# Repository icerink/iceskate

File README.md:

# iceskate

A low cost FPGA development board for absolute newbies.

## Why?
Getting started with FPGA design is hard. Unnecessarily hard.

## How?
Everyone knows how to use a browser. Many people know (some) webdesign.

The [*icerink*](https://github.com/icerink) ecosystem tries to exploit this by building a complete browser centric FPGA workflow. Edit, synthesize and upload FPGA designs from within your browser.

Doing this lowers the boarding hurdle by not requiring the installation of toolchains. Just plug in the board and begin to play :).

## What?
Mainly a FPGA and a USB interface. Not much more. 

The main source of inspiration for this board was the [upduino](http://gnarlygrey.atspace.cc/development-platform.html) by Gnarly Grey. We tried to build a similarly minimal and cheap board. The main Hardware feature, our board employs additionally, is the Microcontroller that is capable of speaking a wide variety of USB-Protocols.

In the *icerink* ecosystem, this capability is used to access the FPGA board from within the browser. 

The iceskate board features:
* The [ICE40UP5K](http://datasheet.octopart.com/ICE40UP5K-SG48ITR50-Lattice-Semiconductor-datasheet-101745901.pdf) FPGA (with experimential support in project icestorm, an open source fpga toolchain)
* An [STM32F070F6P6](http://datasheet.octopart.com/STM32F070F6P6-STMicroelectronics-datasheet-36993117.pdf)
* A single user definable push button and
* A user definable LED

## How to get one?
Build one yourself!

The board is optimized for hand soldering and has a [BOM cost](https://octopart.com/bom-tool/w8mU938s) of ~10€ when you build 10. The PCB can be ordered online at most common PCB manufacturers. We Ordered our boards at jlcpcb. 
[Assembly instructiost can be found here.](https://icerink.github.io/iceskate/)

## Can I help?
Definitely.

If you want to contribute to the hardware design or help with any other thing, do not hesitate to use the issue tracker to get in touch :).

However, it would be nice if you talk to us, **before** you start writing code and invest your time ;).

To develop the board, clone this repository with 
`git clone --recursive https://github.com/icerink/iceskate`.
Then you can simply use Kicad to edit the scematics and PCB.

```diff
- Warning!
- This Project uses submodules! when you clone without --recursive Kicad wont find some libraries!
```

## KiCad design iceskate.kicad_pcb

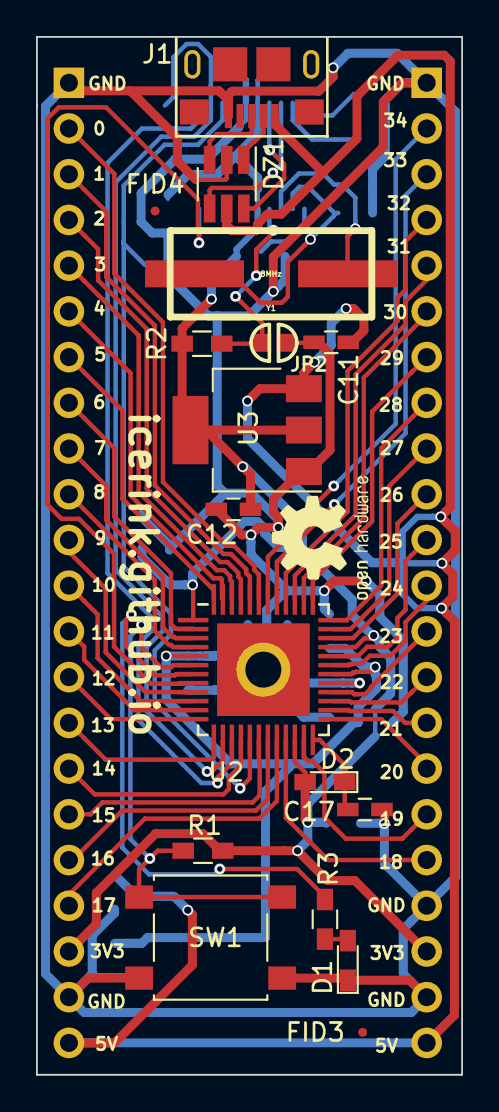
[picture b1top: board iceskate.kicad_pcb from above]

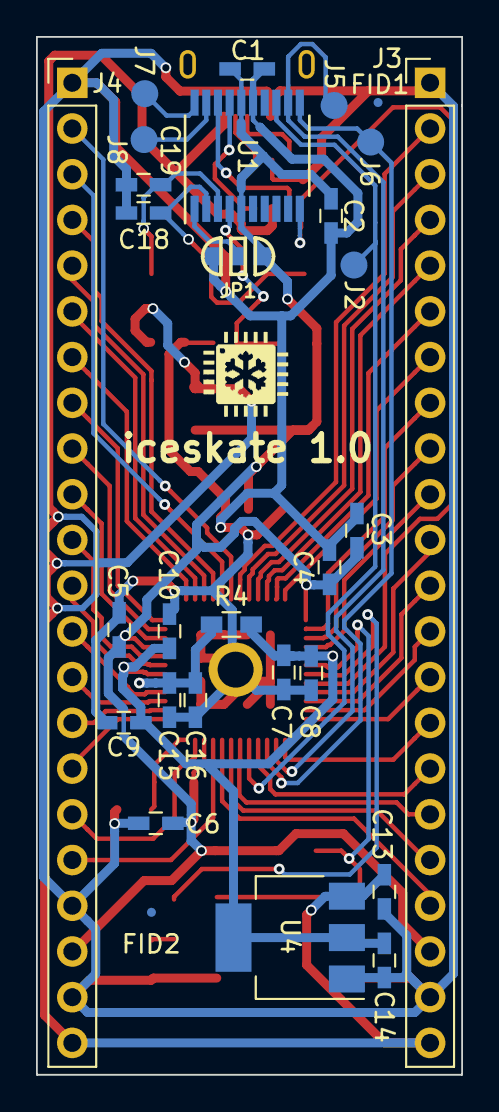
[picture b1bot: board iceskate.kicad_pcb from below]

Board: 2 copper layers, 23.6 x 57.7 mm, 47 parts (30 on the bottom side), 58 nets.

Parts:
C1, C2: C; C_0603_HandSoldering
C3, C6, C7, C10, C11, C12, C13, C14, C16, C17: 1µ; C_0603_HandSoldering
C4, C5, C8, C9, C15: 0.1µ; C_0603_HandSoldering
C18, C19: 22p; C_0603_HandSoldering
D1: LED; LED_0603_HandSoldering
D2: D; LED_0603_HandSoldering
DZ1: USBLC6-2SC6; SOT-23-6_Handsoldering
FID1, FID2, FID3, FID4: FIDUCIAL; Fiducial_0.5mm_Dia_1mm_Outer
J1: USB_OTG; FCI_10118193-0001LF
J2, J5, J6, J7, J8: TEST_1P; Measurement_Point_Round-SMD-Pad_Small
J3, J4: Conn_01x22; Pin_Header_Straight_1x22_Pitch2.54mm
JP1: Jumper_NC_Dual; SOLDER-JUMPER_2-WAY
JP2: Jumper; SOLDER-JUMPER_1-WAY
LOGO: logo
R1, R2: 10k; R_0603_HandSoldering
R3: 100; R_0603_HandSoldering
R4: 10; R_0603_HandSoldering
SW1: SW_Push; SW_SPST_B3S-1000
U1: STM32F070F6P6; TSSOP-20_4.4x6.5mm_Pitch0.65mm
U2: ICE40UP5K-SG48; QFN-48-1EP_7x7mm_Pitch0.5mm
U3: LD1117S33TR_SOT223; SOT-223-3_TabPin2
U4: LD1117S12TR_SOT223; SOT-223-3_TabPin2
Y1: 8MHz; HC49%2fUS

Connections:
+1V2: C7.1, C8.1, C9.1, C10.1, C14.1, R4.1, U2.5, U2.30, U4.2
+2V5: C17.1, D2.1, U2.24
+3V3: C1.1, C2.1, C3.1, C4.1, C5.1, C6.1, C12.1, D2.2, J3.20, J4.20, JP1.3, R1.1, R2.2, U1.5, U1.16, U2.1, U2.22, U2.33, U3.2
+5V: C11.1, C13.1, DZ1.5, J1.1, J3.22, J4.22, U3.3, U4.3
/IO_0: J3.2, U2.43
/IO_1: J3.3, U2.44
/IO_2: J3.4, U2.45
/IO_3: J3.5, U2.46
/IO_4: J3.6, U2.47
/IO_5: J3.7, U2.48
/IO_6: J3.8, U2.2
/IO_7: J3.9, U2.3
/IO_8: J3.10, U2.4
/IO_9: J3.11, U2.9
/IO_10: J3.12, U2.10
/IO_11: J3.13, U2.11
/IO_12: J3.14, U2.12
/IO_13: J3.15, U2.13
/IO_14: J3.16, U2.16
/IO_15: J3.17, U2.18
/IO_16: J3.18, U2.19
/IO_17: J3.19, U2.20
/IO_18: J4.18, U2.21
/IO_19: J4.17, U2.23
/IO_20: J4.16, U2.25
/IO_21: J4.15, U2.26
/IO_22: J4.14, U2.27
/IO_23: J4.13, U2.28
/IO_24: J4.12, U2.31
/IO_25: J4.11, U2.32
/IO_26: J4.10, U2.34
/IO_27: J4.9, U2.35
/IO_28: J4.8, U2.36
/IO_29: J4.7, U2.37
/IO_30: J4.6, U2.38
/IO_31: J4.5, U2.39
/IO_32: J4.4, U2.40
/IO_33: J4.3, U2.41
/IO_34: J4.2, U2.42
/IO_BTN: R1.2, SW1.1, U2.6
/IO_LED: R3.2, U2.7
/RESET: U1.10, U2.8
/SPI_MISO: J5.1, U1.12, U2.14
/SPI_MOSI: J2.1, U1.13, U2.17
/SPI_SCK: J6.1, U1.11, U2.15
/USB_D+: DZ1.4, U1.18
/USB_D-: DZ1.6, U1.17
GND: C1.2, C2.2, C3.2, C4.2, C5.2, C6.2, C7.2, C8.2, C9.2, C10.2, C11.2, C12.2, C13.2, C14.2, C15.2, C16.2, C17.2, C18.1, C19.2, D1.1, DZ1.2, J1.5, J3.1, J3.21, J4.1, J4.19, J4.21, JP1.1, JP2.1, SW1.2, U1.15, U2.49, U3.1, U4.1
unnamed: C15.1, C16.1, R4.2, U2.29
unnamed: C18.2, U1.2, Y1.2
unnamed: C19.1, U1.3, Y1.1
unnamed: D1.2, R3.1
unnamed: DZ1.1, J1.2
unnamed: DZ1.3, J1.3
unnamed: J7.1, U1.20
unnamed: J8.1, U1.19
unnamed: JP1.2, U1.1
unnamed: JP2.2, R2.1, U1.4

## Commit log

2018-04-21 initial schematic
2018-04-21 begin placing
2018-04-21 add basic docs and license
2018-04-21 lalalal
2018-04-21 ignore vscode files
2018-04-22 fully layouted; ready to use ;)
2018-04-22 add basic rendering
2018-04-22 minor corrections
2018-04-23 add logo
2018-04-23 add remaining 3d models; closes #3
2018-04-23 add crystal and usb esd; crystal has to be somwhere else
2018-04-23 move crystal to be not _that_ bad
2018-04-24 add silkscreen layout + logos; closes #1
2018-04-30 add io labels; optimize silkscreen
2018-04-30 update rendering
2018-04-30 replace failed rendering
2018-04-30 rename project files
2019-01-02 add assembly instructions
2019-01-02 add link to assembly instructions
2019-01-02 fix link
